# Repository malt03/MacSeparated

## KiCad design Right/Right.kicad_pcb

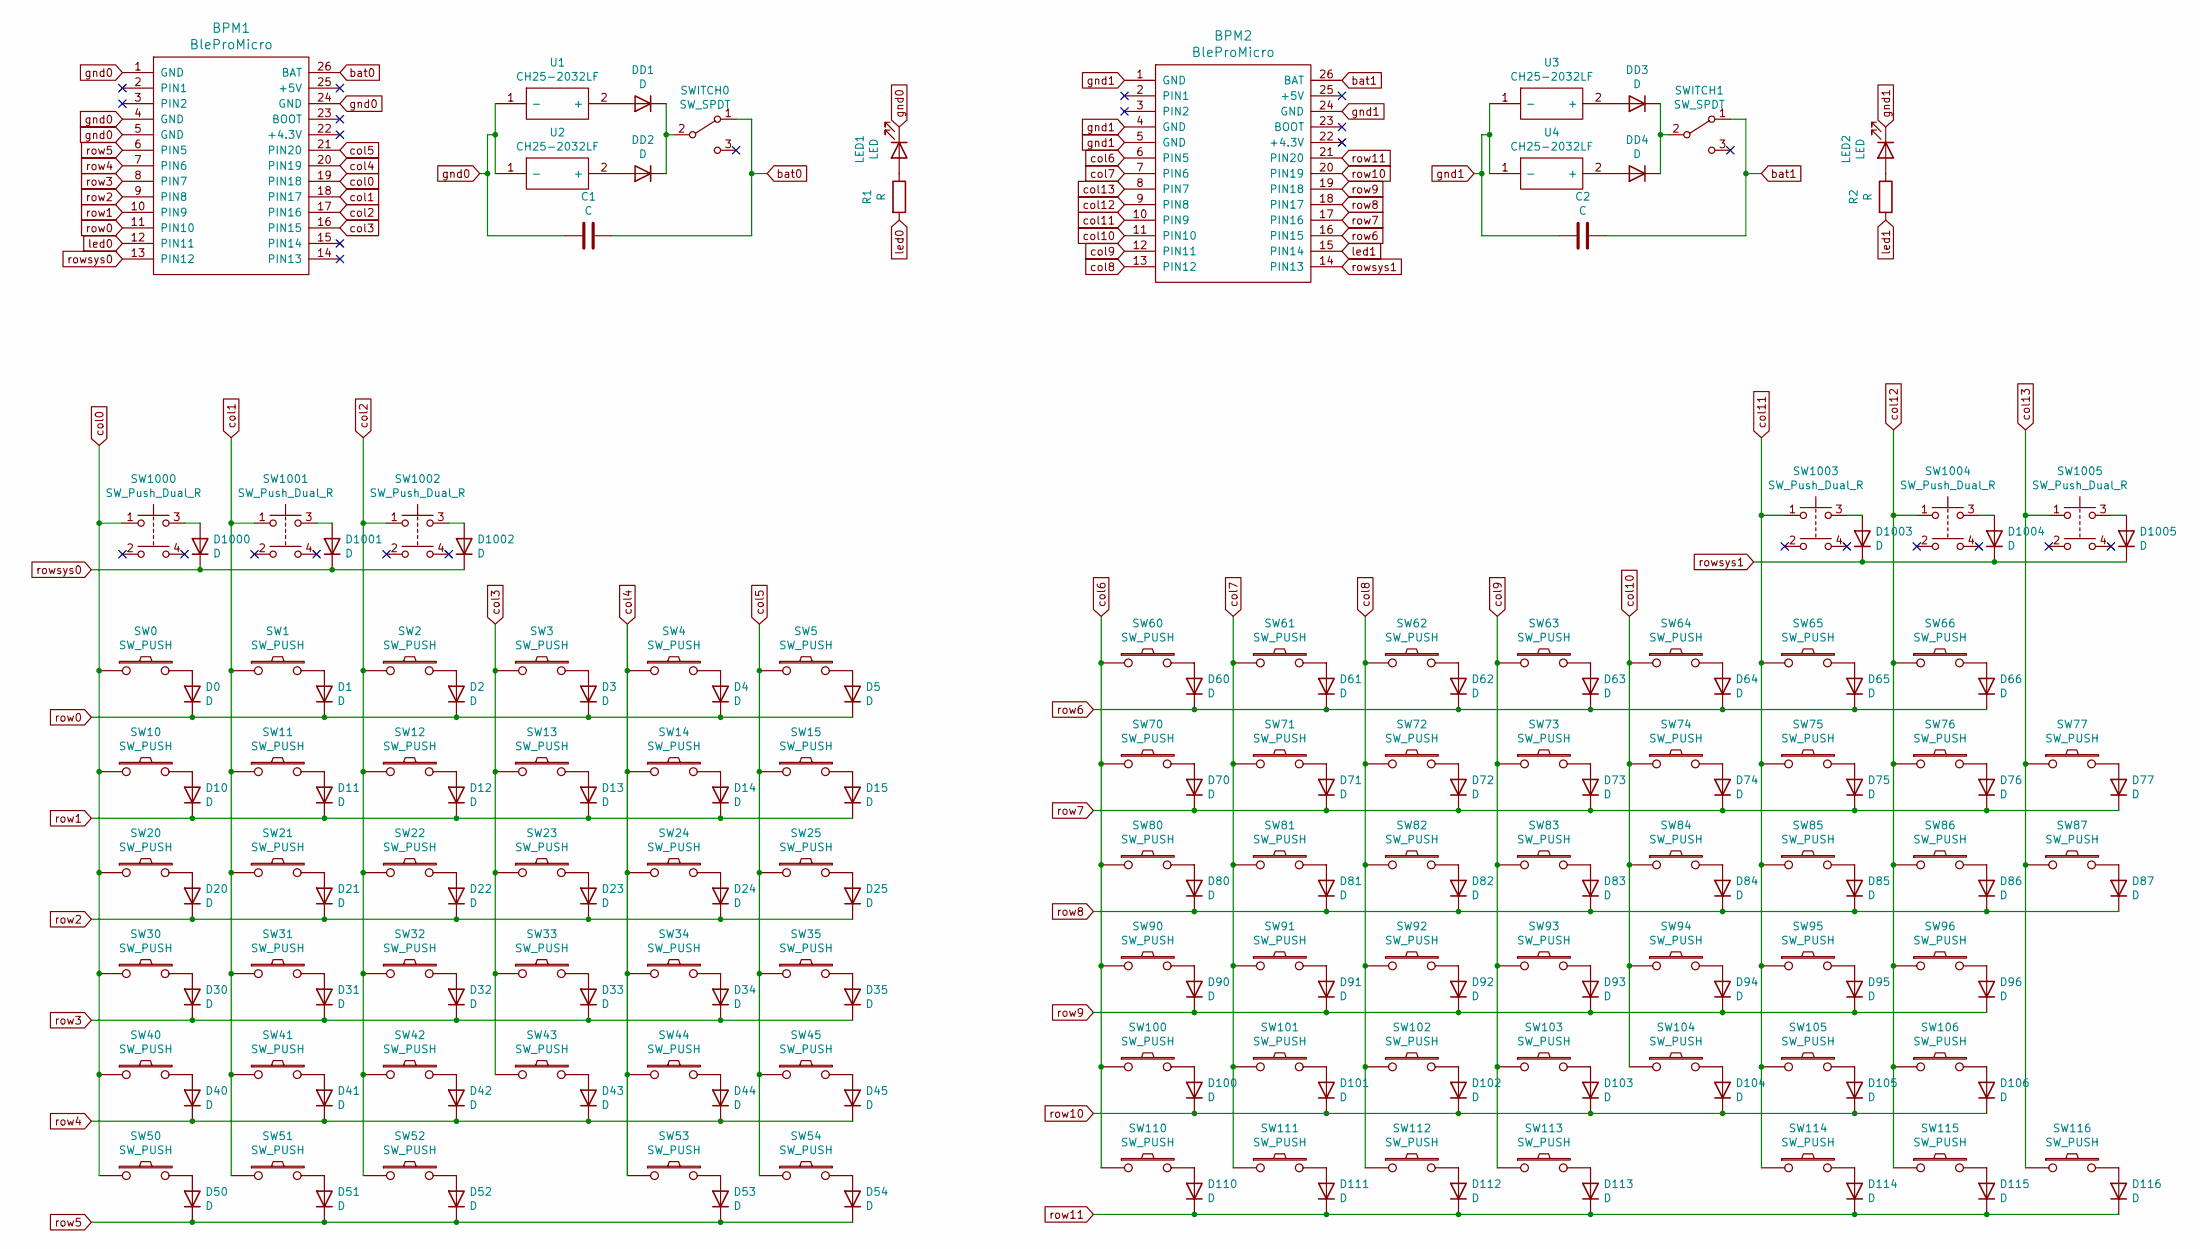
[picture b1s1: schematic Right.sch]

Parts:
BPM1, BPM2: BleProMicro; BLEMicroPro_reversed
C1, C2: C; C_Disc_D5.1mm_W3.2mm_P5.00mm
D0, D1, D2, D3, D4, D5, D10, D11, D12, D13, D14, D15, D20, D21, D22, D23, D24, D25, D30, D31, D32, D33, D34, D35, D40, D41, D42, D43, D44, D45, D50, D51, D52, D53, D54, D60, D61, D62, D63, D64, D65, D66, D70, D71, D72, D73, D74, D75, D76, D77, D80, D81, D82, D83, D84, D85, D86, D87, D90, D91, D92, D93, D94, D95, D96, D100, D101, D102, D103, D104, D105, D106, D110, D111, D112, D113, D114, D115, D116, D1000, D1001, D1002, D1003, D1004, D1005: D; D_DO-35_SOD27_P7.62mm_Horizontal
DD1, DD2, DD3, DD4: D; D_DO-41_SOD81_P7.62mm_Horizontal
LED1, LED2: LED; LED_D3.0mm
R1, R2: R; R_Axial_DIN0204_L3.6mm_D1.6mm_P7.62mm_Horizontal
SW0, SW1, SW2, SW3, SW4, SW5, SW10, SW11, SW12, SW13, SW14, SW15, SW20, SW21, SW22, SW23, SW24, SW25, SW30, SW31, SW32, SW33, SW34, SW35, SW40, SW41, SW42, SW43, SW44, SW45, SW50, SW51, SW52, SW53, SW54, SW60, SW61, SW62, SW63, SW64, SW65, SW66, SW70, SW71, SW72, SW73, SW74, SW75, SW76, SW77, SW80, SW81, SW82, SW83, SW84, SW85, SW86, SW87, SW90, SW91, SW92, SW93, SW94, SW95, SW96, SW100, SW101, SW102, SW103, SW104, SW105, SW106, SW110, SW111, SW112, SW113, SW114, SW115, SW116: SW_PUSH; Kailh_socket_MX
SW1000, SW1001, SW1002, SW1003, SW1004, SW1005: SW_Push_Dual_R; SW_TH_Tactile_Omron_B3F-10xx
SWITCH0, SWITCH1: SW_SPDT; 2MS1-T1-B4-VS2-Q-E-S
U1, U2, U3, U4: CH25-2032LF; CH252032LF; Manufacturer_Part_Number CH25-2032LF

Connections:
unnamed: D0.2 (A), SW0.2
unnamed: D1.2 (A), SW1.2
unnamed: D2.2 (A), SW2.2
unnamed: D3.2 (A), SW3.2
unnamed: D4.2 (A), SW4.2
unnamed: D5.2 (A), SW5.2
unnamed: D10.2 (A), SW10.2
unnamed: D11.2 (A), SW11.2
unnamed: D12.2 (A), SW12.2
unnamed: D13.2 (A), SW13.2
unnamed: D14.2 (A), SW14.2
unnamed: D15.2 (A), SW15.2
unnamed: D20.2 (A), SW20.2
unnamed: D21.2 (A), SW21.2
unnamed: D22.2 (A), SW22.2
unnamed: D23.2 (A), SW23.2
unnamed: D24.2 (A), SW24.2
unnamed: D25.2 (A), SW25.2
unnamed: D30.2 (A), SW30.2
unnamed: D31.2 (A), SW31.2
unnamed: D32.2 (A), SW32.2
unnamed: D33.2 (A), SW33.2
unnamed: D34.2 (A), SW34.2
unnamed: D35.2 (A), SW35.2
unnamed: D40.2 (A), SW40.2
unnamed: D41.2 (A), SW41.2
unnamed: D42.2 (A), SW42.2
unnamed: D43.2 (A), SW43.2
unnamed: D44.2 (A), SW44.2
unnamed: D45.2 (A), SW45.2
unnamed: D50.2 (A), SW50.2
unnamed: D51.2 (A), SW51.2
unnamed: D52.2 (A), SW52.2
unnamed: D53.2 (A), SW53.2
unnamed: D54.2 (A), SW54.2
unnamed: D60.2 (A), SW60.2
unnamed: D61.2 (A), SW61.2
unnamed: D62.2 (A), SW62.2
unnamed: D63.2 (A), SW63.2
unnamed: D64.2 (A), SW64.2
unnamed: D65.2 (A), SW65.2
unnamed: D66.2 (A), SW66.2
unnamed: D70.2 (A), SW70.2
unnamed: D71.2 (A), SW71.2
unnamed: D72.2 (A), SW72.2
unnamed: D73.2 (A), SW73.2
unnamed: D74.2 (A), SW74.2
unnamed: D75.2 (A), SW75.2
unnamed: D76.2 (A), SW76.2
unnamed: D77.2 (A), SW77.2
unnamed: D80.2 (A), SW80.2
unnamed: D81.2 (A), SW81.2
unnamed: D82.2 (A), SW82.2
unnamed: D83.2 (A), SW83.2
unnamed: D84.2 (A), SW84.2
unnamed: D85.2 (A), SW85.2
unnamed: D86.2 (A), SW86.2
unnamed: D87.2 (A), SW87.2
unnamed: D90.2 (A), SW90.2
unnamed: D91.2 (A), SW91.2
unnamed: D92.2 (A), SW92.2
unnamed: D93.2 (A), SW93.2
unnamed: D94.2 (A), SW94.2
unnamed: D95.2 (A), SW95.2
unnamed: D96.2 (A), SW96.2
unnamed: D100.2 (A), SW100.2
unnamed: D101.2 (A), SW101.2
unnamed: D102.2 (A), SW102.2
unnamed: D103.2 (A), SW103.2
unnamed: D104.2 (A), SW104.2
unnamed: D105.2 (A), SW105.2
unnamed: D106.2 (A), SW106.2
unnamed: D110.2 (A), SW110.2
unnamed: D111.2 (A), SW111.2
unnamed: D112.2 (A), SW112.2
unnamed: D113.2 (A), SW113.2
unnamed: D114.2 (A), SW114.2
unnamed: D115.2 (A), SW115.2
unnamed: D116.2 (A), SW116.2
unnamed: D1000.2 (A), SW1000.3
unnamed: D1001.2 (A), SW1001.3
unnamed: D1002.2 (A), SW1002.3
unnamed: D1003.2 (A), SW1003.3
unnamed: D1004.2 (A), SW1004.3
unnamed: D1005.2 (A), SW1005.3
unnamed: DD1.1 (K), DD2.1 (K), SWITCH0.2 (B)
unnamed: DD1.2 (A), U1.2 (+)
unnamed: DD2.2 (A), U2.2 (+)
unnamed: DD3.1 (K), DD4.1 (K), SWITCH1.2 (B)
unnamed: DD3.2 (A), U3.2 (+)
unnamed: DD4.2 (A), U4.2 (+)
unnamed: LED1.2 (A), R1.1
unnamed: LED2.2 (A), R2.1
bat0: BPM1.26 (BAT), C1.1, SWITCH0.1 (A)
bat1: BPM2.26 (BAT), C2.1, SWITCH1.1 (A)
col0: BPM1.19 (PIN18), SW0.1, SW10.1, SW20.1, SW30.1, SW40.1, SW50.1, SW1000.1
col1: BPM1.18 (PIN17), SW1.1, SW11.1, SW21.1, SW31.1, SW41.1, SW51.1, SW1001.1
col2: BPM1.17 (PIN16), SW2.1, SW12.1, SW22.1, SW32.1, SW42.1, SW52.1, SW1002.1
col3: BPM1.16 (PIN15), SW3.1, SW13.1, SW23.1, SW33.1, SW43.1
col4: BPM1.20 (PIN19), SW4.1, SW14.1, SW24.1, SW34.1, SW44.1, SW53.1
col5: BPM1.21 (PIN20), SW5.1, SW15.1, SW25.1, SW35.1, SW45.1, SW54.1
col6: BPM2.6 (PIN5), SW60.1, SW70.1, SW80.1, SW90.1, SW100.1, SW110.1
col7: BPM2.7 (PIN6), SW61.1, SW71.1, SW81.1, SW91.1, SW101.1, SW111.1
col8: BPM2.13 (PIN12), SW62.1, SW72.1, SW82.1, SW92.1, SW102.1, SW112.1
col9: BPM2.12 (PIN11), SW63.1, SW73.1, SW83.1, SW93.1, SW103.1, SW113.1
col10: BPM2.11 (PIN10), SW64.1, SW74.1, SW84.1, SW94.1, SW104.1
col11: BPM2.10 (PIN9), SW65.1, SW75.1, SW85.1, SW95.1, SW105.1, SW114.1, SW1003.1
col12: BPM2.9 (PIN8), SW66.1, SW76.1, SW86.1, SW96.1, SW106.1, SW115.1, SW1004.1
col13: BPM2.8 (PIN7), SW77.1, SW87.1, SW116.1, SW1005.1
gnd0: BPM1.1 (GND), BPM1.4 (GND), BPM1.5 (GND), BPM1.24 (GND), C1.2, LED1.1 (K), U1.1 (-), U2.1 (-)
gnd1: BPM2.1 (GND), BPM2.4 (GND), BPM2.5 (GND), BPM2.24 (GND), C2.2, LED2.1 (K), U3.1 (-), U4.1 (-)
led0: BPM1.12 (PIN11), R1.2
led1: BPM2.15 (PIN14), R2.2
row0: BPM1.11 (PIN10), D0.1 (K), D1.1 (K), D2.1 (K), D3.1 (K), D4.1 (K), D5.1 (K)
row1: BPM1.10 (PIN9), D10.1 (K), D11.1 (K), D12.1 (K), D13.1 (K), D14.1 (K), D15.1 (K)
row2: BPM1.9 (PIN8), D20.1 (K), D21.1 (K), D22.1 (K), D23.1 (K), D24.1 (K), D25.1 (K)
row3: BPM1.8 (PIN7), D30.1 (K), D31.1 (K), D32.1 (K), D33.1 (K), D34.1 (K), D35.1 (K)
row4: BPM1.7 (PIN6), D40.1 (K), D41.1 (K), D42.1 (K), D43.1 (K), D44.1 (K), D45.1 (K)
row5: BPM1.6 (PIN5), D50.1 (K), D51.1 (K), D52.1 (K), D53.1 (K), D54.1 (K)
row6: BPM2.16 (PIN15), D60.1 (K), D61.1 (K), D62.1 (K), D63.1 (K), D64.1 (K), D65.1 (K), D66.1 (K)
row7: BPM2.17 (PIN16), D70.1 (K), D71.1 (K), D72.1 (K), D73.1 (K), D74.1 (K), D75.1 (K), D76.1 (K), D77.1 (K)
row8: BPM2.18 (PIN17), D80.1 (K), D81.1 (K), D82.1 (K), D83.1 (K), D84.1 (K), D85.1 (K), D86.1 (K), D87.1 (K)
row9: BPM2.19 (PIN18), D90.1 (K), D91.1 (K), D92.1 (K), D93.1 (K), D94.1 (K), D95.1 (K), D96.1 (K)
row10: BPM2.20 (PIN19), D100.1 (K), D101.1 (K), D102.1 (K), D103.1 (K), D104.1 (K), D105.1 (K), D106.1 (K)
row11: BPM2.21 (PIN20), D110.1 (K), D111.1 (K), D112.1 (K), D113.1 (K), D114.1 (K), D115.1 (K), D116.1 (K)
rowsys0: BPM1.13 (PIN12), D1000.1 (K), D1001.1 (K), D1002.1 (K)
rowsys1: BPM2.14 (PIN13), D1003.1 (K), D1004.1 (K), D1005.1 (K)

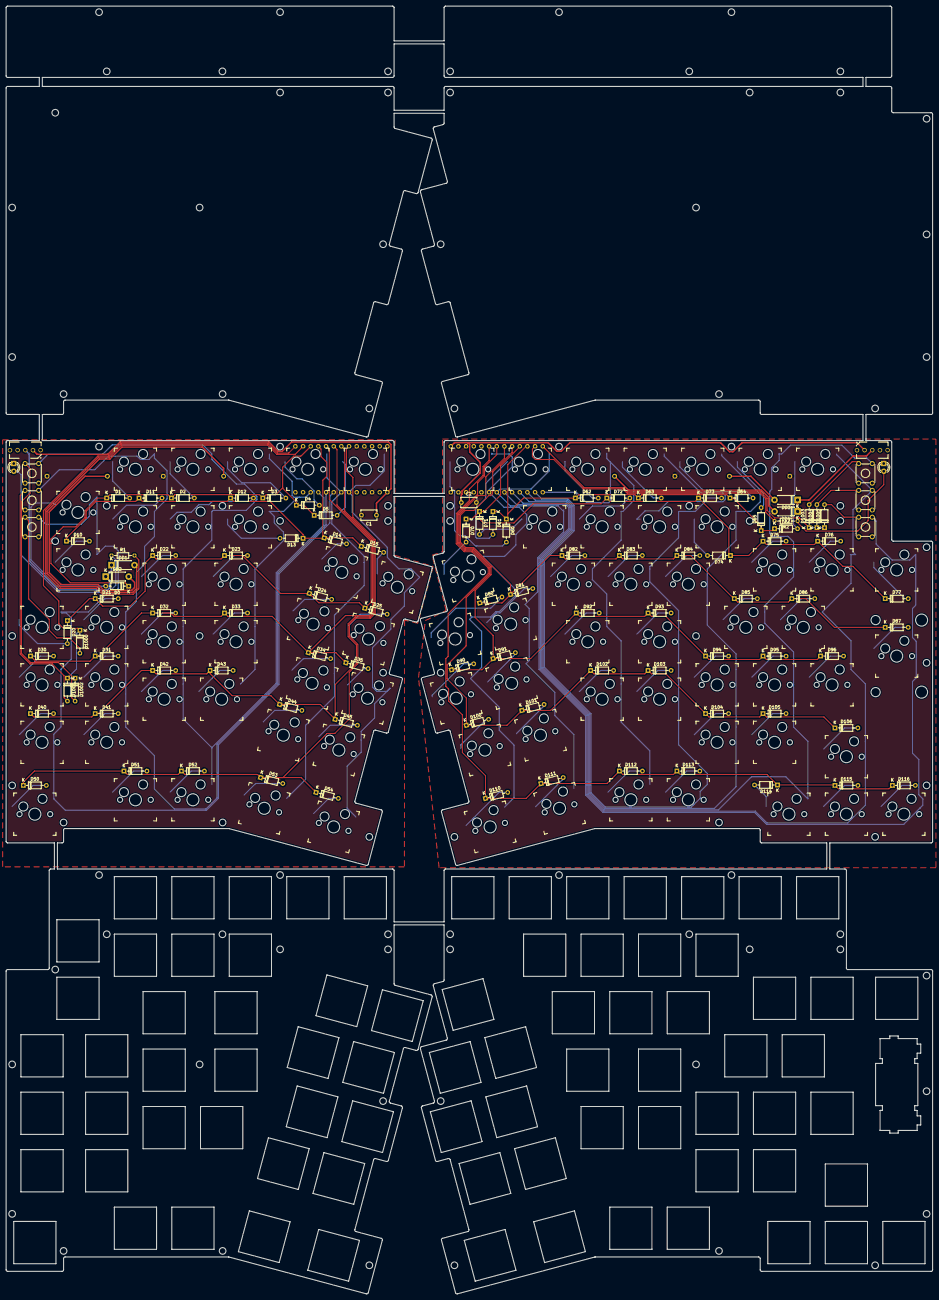
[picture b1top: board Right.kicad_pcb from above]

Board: 2 copper layers, 307.1 x 426.8 mm, 188 parts (0 on the bottom side), 127 nets.

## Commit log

2020-08-14 first
2020-08-17 電池位置調整
2020-08-17 配線整理
2020-08-17 配線に余裕をつくる
2020-08-17 位置調整
2020-08-19 外枠とスペーサー
2020-08-25 全体にした
2020-08-26 とりあえず右手全部つながった
2020-08-26 右手で来た
2020-08-26 左手調整中
2020-08-26 左手ボタン位置調整
2020-08-26 左手外枠できた
2020-08-26 なんか裏返ってた
2020-08-27 いろいろできてきた
2020-08-28 トッププレート途中
2020-08-28 右手トッププレート
2020-08-28 トッププレート
2020-08-28 左手導線
2020-08-28 配線できた
2020-09-01 左手穴あけ
2020-09-02 左穴できた
2020-09-02 error
2020-09-03 spacer
2020-09-04 rename
